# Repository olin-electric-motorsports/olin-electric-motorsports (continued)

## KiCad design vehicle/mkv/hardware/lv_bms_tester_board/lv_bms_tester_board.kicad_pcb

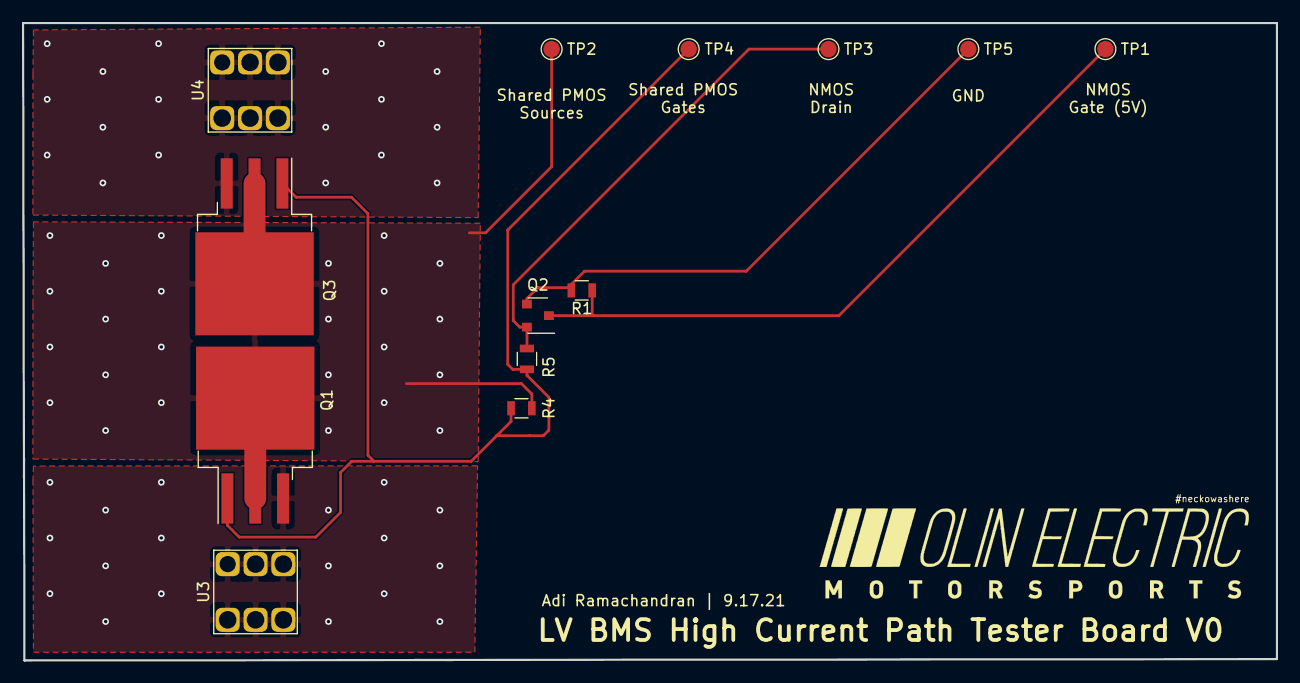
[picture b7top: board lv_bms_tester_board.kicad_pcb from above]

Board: 4 copper layers, 114.3 x 58.1 mm, 13 parts (0 on the bottom side), 7 nets.

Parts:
Q1, Q3: SQM110P06; TO-263-3-TabPin2
Q2: MMBF170; SOT-23-3_OEM
R1: R_100K; R_0805_OEM
R4: R_10K; R_0805_OEM
R5: R_10; R_0805_OEM
TP1, TP2, TP3, TP4, TP5: Test_Point_SMD; TestPoint_Pad_D1.5mm
U3, U4: redcube-7461057; redcube_pressfit_6pin

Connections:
GND: Q2.2, R1.2, TP5.1
unnamed: Q1.1, Q3.1, R4.2, R5.1, TP4.1
unnamed: Q1.2, Q3.2, R4.1, TP2.1
unnamed: Q1.3, U3.1
unnamed: Q2.1, R1.1, TP1.1
unnamed: Q2.3, R5.2, TP3.1
unnamed: Q3.3, U4.1

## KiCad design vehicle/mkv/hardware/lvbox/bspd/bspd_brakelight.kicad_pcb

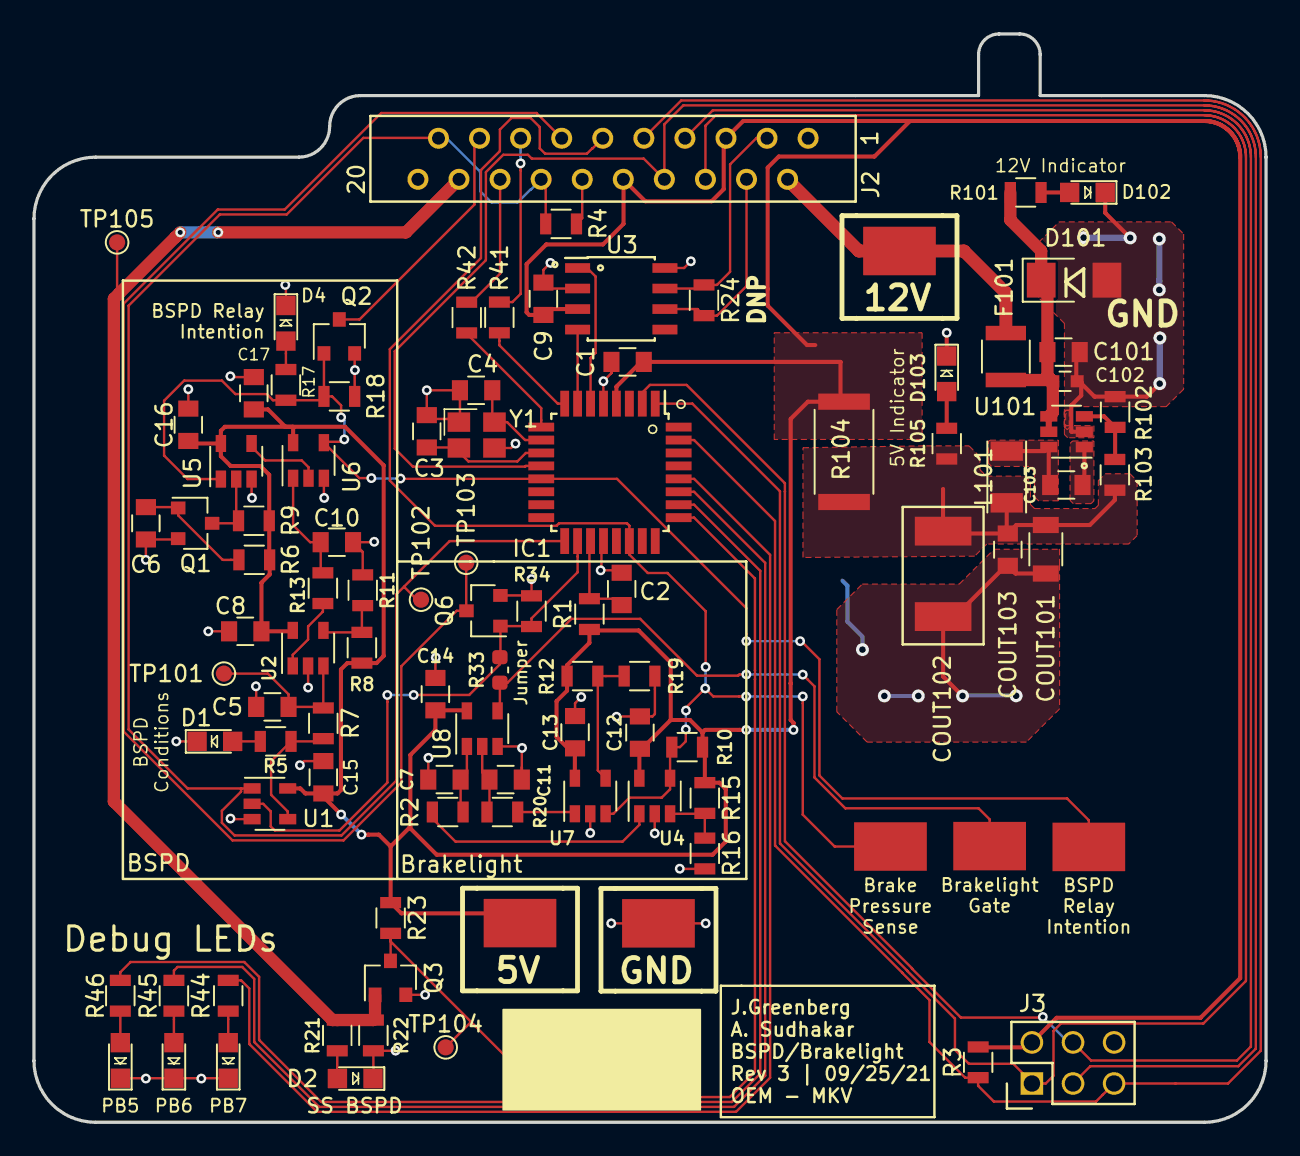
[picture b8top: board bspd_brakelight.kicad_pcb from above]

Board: 2 copper layers, 76.2 x 67.3 mm, 97 parts (0 on the bottom side), 57 nets.

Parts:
C1, C6, C8, C9, C12, C13, C14, C15, C16, C17, C101, C103: C_0.1uF; C_0805_OEM
C2: C_100pF; C_0805_OEM
C3, C4: C_30pF; C_0805_OEM
C5: C_10uF; C_0805_OEM
C7, C10, C11: C_1uF; C_0805_OEM
C102: C_2.2uF; C_0603
COUT101: C_22uF; C_1206_OEM
COUT102: C_33uF; Fuse_1812
COUT103: C_47uF; C_0805_OEM
D1, D2, D4, D5, D12, D13, D102, D103: LED_0805; LED_0805_OEM
D101: D_Zener_18V; DO-214AA
F101: F_500mA_16V; Fuse_1210
IC1: ATMEGA16M1; TQFP-32_7x7mm_Pitch0.8mm
J2: MM_F_RA_20; micromatch_female_ra_20
J3: CONN_02X03; Pin_Header_Straight_2x03
L101: L_100uH; L_100uH_OEM
Q1, Q2, Q3, Q6: SSM3K333R; SOT-23F
R1: R_100; R_0805_OEM
R2, R6, R8, R10, R11, R13, R15, R18, R20, R21, R23, R34: R_10K; R_0805_OEM
R3: R_10k; R_0805_OEM
R4, R9, R22, R103: R_100K; R_0805_OEM
R5, R17, R41, R42, R44, R45, R46, R105: R_200; R_0805_OEM
R7: R_71.5K; R_0805_OEM
R12: R_2.2K; R_0805_OEM
R16, R101: R_1K; R_0805_OEM
R19: R_499; R_0805_OEM
R24: R_120_DNP; R_0805_OEM
R33: R_0; R_0603_1608Metric
R102: R_25K; R_0805_OEM
R104: R_0_2512; R_2512_OEM
TP1, TP2, TP3, TP4, TP5, TP6: Test_Point_SMD
TP101, TP102, TP103, TP104, TP105: Test_Point_SMD; TestPoint_Pad_D1.0mm
U1: SN74LVC1G08; SOT-23-5_OEM
U2, U4, U7: MCP6001; SOT-23-5_OEM
U3: CAN_Transceiver; SOIC-8_3.9x4.9mm_Pitch1.27mm_OEM
U5, U6: SN74LVC1G02; SOT-23-5_OEM
U8: SN74LVC1G32; SOT-23-5_OEM
U101: TPS560430YF; SOT-23-6_OEM
Y1: Crystal_SMD; Crystal_SMD_FA238

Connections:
+12V: F101.2, J2.2, TP4.1
/BRAKELIGHT_GATE: IC1.18, Q6.1, R33.1, R34.1, U1.2
/BRAKELIGHT_LSD: J2.13, Q6.3, TP103.1
/BRAKE_PRESSURE_SENSE: IC1.22, J2.11, R10.2, TP1.1, U4.4, U7.3
/BSPD_CURRENT_SENSE: IC1.17, J2.14, J2.19, R4.2, TP102.1, U1.1
/BSPD_RELAY_INTENTION: IC1.13, Q2.1, R17.1, R18.1, TP3.1, U5.1, U6.4
/BSPD_RELAY_LSD: J2.17, Q2.3
/CAN_HIGH: J2.3, R24.1, U3.7
/CAN_LOW: J2.4, R24.2, U3.6
/DEBUG_LED_1: IC1.26, R46.1
/DEBUG_LED_2: IC1.27, R45.1
/DEBUG_LED_3: IC1.28, R44.1
/MISO: IC1.1, J2.6, J3.1
/MOSI: IC1.2, J2.7, J3.4
/RESET: IC1.31, J2.9, J3.5, R3.2
/RJ45_LED_G: J2.15, R41.1
/RJ45_LED_O: J2.16, R42.2
/RXCAN: IC1.7, U3.4
/SCK: IC1.12, J2.8, J3.3
/SHUTDOWN_SENSE_BSPD: J2.18, Q3.1, R21.1, R22.2, TP105.1
/TXCAN: IC1.6, U3.1
/~SHUTDOWN_SENSE_BSPD_PIN: IC1.25, Q3.3, R23.2, TP104.1
GND: C1.2, C2.2, C3.2, C4.2, C5.2, C6.2, C7.2, C8.2, C9.2, C10.2, C11.2, C12.2, C13.2, C14.2, C15.2, C16.2, C17.2, C101.2, C102.2, COUT101.2, COUT102.2, COUT103.2, D1.1, D2.1, D4.1, D5.1, D12.1, D13.1, D101.2, D102.1, D103.1, IC1.5, IC1.20, J2.1, J2.12, J2.20, J3.6, Q1.2, Q2.2, Q3.2, Q6.2, R4.1, R11.2, R16.2, R18.2, R19.1, R22.1, R34.2, R102.2, TP6.1, U1.3, U2.2, U3.2, U3.8, U4.2, U5.3, U6.3, U7.2, U8.3, U101.2, Y1.2, Y1.4
unnamed: C2.1, IC1.19, R1.2
unnamed: C3.1, IC1.11, Y1.1
unnamed: C4.1, IC1.10, Y1.3
unnamed: C5.1, R7.2, TP101.1, U2.3
unnamed: C6.1, Q1.1, R6.2
unnamed: C7.1, R2.1, U8.1
unnamed: C10.1, R13.1, U6.1
unnamed: C11.1, R20.1, U8.2
unnamed: C101.1, C102.1, D101.1, F101.1, R101.1, U101.4, U101.5
unnamed: C103.1, L101.1, U101.6
unnamed: C103.2, U101.1
unnamed: COUT101.1, COUT102.1, COUT103.1, L101.2, R103.1, R104.2, R105.1
unnamed: D1.2, R5.2
unnamed: D2.2, R21.2
unnamed: D4.2, R17.2
unnamed: D5.2, R44.2
unnamed: D12.2, R45.2
unnamed: D13.2, R46.2
unnamed: D102.2, R101.2
unnamed: D103.2, R105.2
unnamed: IC1.8, R41.2
unnamed: IC1.9, R42.1
unnamed: Q1.3, R9.1, U5.2
unnamed: R2.2, U4.1
unnamed: R5.1, R7.1, U1.4
unnamed: R8.2, R11.1, U2.4
unnamed: R12.1, R19.2, U7.4
unnamed: R13.2, U2.1
unnamed: R15.2, R16.1, U4.3
unnamed: R20.2, U7.1
unnamed: R33.2, TP2.1, U8.4
unnamed: R102.1, R103.2, U101.3
unnamed: U5.4, U6.2
VCC: C1.1, C8.1, C9.1, C12.1, C13.1, C14.1, C15.1, C16.1, C17.1, IC1.4, J2.5, J2.10, J3.2, R1.1, R3.1, R6.1, R8.1, R9.2, R10.1, R12.2, R15.1, R23.1, R104.1, TP5.1, U1.5, U2.5, U3.3, U4.5, U5.5, U6.5, U7.5, U8.5

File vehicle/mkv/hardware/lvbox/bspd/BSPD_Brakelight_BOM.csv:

Reference, Quantity, Value, Footprint, Datasheet, MFN, MPN, Package, PurchasingLink, Digi-key Part Number, Link, Purchasing Link
C10 C7 C11 ,3,"C_1uF","footprints:C_0805_OEM","http://www.samsungsem.com/kr/support/product-search/mlcc/__i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","DK","1276-2887-1-ND","","https://www.digikey.com/product-detail/en/samsung-electro-me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","","",""
C102 ,1,"C_2.2uF","footprints:C_0603_1608Metric","http://www.yageo.com/documents/recent/UPY-GPHC_X5R_4V-to-50V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","DK","311-1451-1-ND","","https://www.digikey.com/product-detail/en/yageo/CC0603KRX5R6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","","",""
C2 ,1,"C_100pF","footprints:C_0805_OEM","https://katalog.we-online.de/pbs/datasheet/885012007057.pdf","DK","732-7852-1-ND","Value","https://www.digikey.com/product-detail/en/wurth-electronics-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","","",""
C4 C3 ,2,"C_30pF","footprints:C_0805_OEM","https://media.digikey.com/pdf/Data%20Sheets/Samsung%20PDFs/C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","DK","1276-1130-1-ND","Value","https://www.digikey.com/product-detail/en/samsung-electro-me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","","",""
C5 ,1,"C_10uF","footprints:C_0805_OEM","http://www.samsungsem.com/kr/support/product-search/mlcc/__i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","DK","1276-1052-1-ND","","https://www.digikey.com/product-detail/en/samsung-electro-me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","","",""
C9 C8 C6 C1 C101 C103 C13 C12 C14 C15 C17 C16 ,12,"C_0.1uF","footprints:C_0805_OEM","http://datasheets.avx.com/X7RDielectric.pdf","DK","478-3352-1-ND","Value","https://www.digikey.com/products/en?keywords=478-3352-1-ND","","",""
COUT101 ,1,"C_22uF","footprints:C_1206_OEM","https://product.tdk.com/info/en/catalog/datasheets/mlcc_comm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","DK","445-11693-1-ND","","https://www.digikey.com/product-detail/en/tdk-corporation/C3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","","",""
COUT102 ,1,"C_33uF","footprints:Fuse_1812","","DK","445-3924-1-ND","","https://www.digikey.com/product-detail/en/tdk-corporation/C4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","","",""
COUT103 ,1,"C_47uF","footprints:C_0805_OEM","http://www.samsungsem.com/kr/support/product-search/mlcc/__i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","DK","1276-6467-1-ND","","https://www.digikey.com/product-detail/en/samsung-electro-me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","","",""
D1 D4 D5 D12 D13 D103 D102 D2 ,8,"LED_0805","footprints:LED_0805_OEM","http://www.osram-os.com/Graphics/XPic9/00078860_0.pdf","DK","475-1410-1-ND","","https://www.digikey.com/products/en?keywords=475-1410-1-ND","","",""
D101 ,1,"D_Zener_18V","footprints:DO-214AA","http://www.mccsemi.com/up_pdf/SMBJ5338B-SMBJ5388B(SMB).pdf","DK","SMBJ5355B-TPMSCT-ND","","https://www.digikey.com/products/en?keywords=SMBJ5355B-TPMSCT-ND","","",""
F101 ,1,"F_500mA_16V","footprints:Fuse_1210","https://belfuse.com/resources/CircuitProtection/datasheets/0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","DK","507-1786-1-ND","","https://www.digikey.com/product-detail/en/bel-fuse-inc/0ZCH0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","","",""
IC1 ,1,"ATMEGA16M1","footprints:TQFP-32_7x7mm_Pitch0.8mm","http://ww1.microchip.com/downloads/en/DeviceDoc/Atmel-8209-8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","DK","ATMEGA16M1-AU-ND","Value","https://www.digikey.com/product-detail/en/atmel/ATMEGA16M1-A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","","",""
J2 ,1,"MM_F_RA_20","footprints:micromatch_female_ra_20","http://www.te.com/commerce/DocumentDelivery/DDEController?Ac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","TE","2-338070-0","","http://www.te.com/usa-en/product-2-338070-0.html","","",""
J3 ,1,"CONN_02X03","footprints:Pin_Header_Straight_2x03","http://portal.fciconnect.com/Comergent//fci/drawing/67996.pdf","DK","609-3234-ND","Value","https://www.digikey.com/product-detail/en/amphenol-fci/67997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","","",""
L101 ,1,"L_100uH","footprints:L_100uH_OEM","","DK","445-15759-1-ND","","https://www.digikey.com/product-detail/en/tdk-corporation/NL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","","https://www.digikey.com/product-detail/en/tdk-corporation/NL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",""
Q1 Q2 Q6 Q3 ,4,"SSM3K333R","footprints:SOT-23F","https://drive.google.com/drive/folders/0B-V-iZf33Y4GNzhDQTJZanJRbVk","DK","SSM3K333RLFCT-ND","","https://www.digikey.com/product-detail/en/toshiba-semiconduc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","","",""
R1 ,1,"R_100","footprints:R_0805_OEM","https://www.seielect.com/Catalog/SEI-rncp.pdf","DK","RNCP0805FTD100RCT-ND","Value","https://www.digikey.com/products/en?keywords=RNCP0805FTD100RCT-ND","","",""
R102 ,1,"R_25K","footprints:R_0805_OEM","","DK","A124124CT-ND","","https://www.digikey.com/product-detail/en/te-connectivity-pa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","CPF-A-0805B25KE","",""
R104 ,1,"R_0_2512","footprints:R_2512_OEM","http://www.te.com/commerce/DocumentDelivery/DDEController?Ac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","DK","A121322CT-ND","","https://www.digikey.com/products/en?keywords=A121322CT-ND","","",""
R12 ,1,"R_2.2K","footprints:R_0805_OEM","https://www.seielect.com/Catalog/SEI-RMCF_RMCP.pdf","DK","RMCF0805FT2K20CT-ND","","https://www.digikey.com/product-detail/en/stackpole-electron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","","",""
R16 R101 ,2,"R_1K","footprints:R_0805_OEM","https://www.seielect.com/Catalog/SEI-rncp.pdf","DK","RNCP0805FTD1K00CT-ND","","https://www.digikey.com/products/en?keywords=RNCP0805FTD1K00CT-ND","","",""
R19 ,1,"R_499","footprints:R_0805_OEM","https://industrial.panasonic.com/cdbs/www-data/pdf/RDA0000/A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","DK","P499CCT-ND","","https://www.digikey.com/product-detail/en/panasonic-electron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","","",""
R24 ,1,"R_120_DNP","footprints:R_0805_OEM","","DK","667-ERJ-6ENF1200V","","https://www.mouser.com/ProductDetail/Panasonic-Industrial-De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","","",""
R3 ,1,"R_10k","footprints:R_0805_OEM","http://www.bourns.com/data/global/pdfs/CRS.pdf","DK","CRS0805-FX-1002ELFCT-ND","Value","https://www.digikey.com/products/en?keywords=CRS0805-FX-1002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","","",""
R33 ,1,"R_0","footprints:R_0603_1608Metric","http://industrial.panasonic.com/www-cgi/jvcr13pz.cgi?E+PZ+3+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","DK","P0.0GCT-ND","","https://www.digikey.com/product-detail/en/panasonic-electron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","","",""
R4 R9 R103 R22 ,4,"R_100K","footprints:R_0805_OEM","https://industrial.panasonic.com/cdbs/www-data/pdf/RDA0000/A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","DK","P100KCCT-ND","","https://www.digikey.com/product-detail/en/panasonic-electron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","","",""
R5 R17 R41 R42 R44 R45 R46 R105 ,8,"R_200","footprints:R_0805_OEM","https://www.seielect.com/Catalog/SEI-RMCF_RMCP.pdf","DK","RMCF0805JT200RCT-ND","","https://www.digikey.com/products/en?keywords=RMCF0805JT200RCT-ND","","",""
R7 ,1,"R_71.5K","footprints:R_0805_OEM","https://industrial.panasonic.com/cdbs/www-data/pdf/RDM0000/A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","DK","P1.07KDACT-ND","","https://www.digikey.com/product-detail/en/panasonic-electron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","","",""
R8 R11 R13 R6 R18 R34 R15 R10 R2 R20 R23 R21 ,12,"R_10K","footprints:R_0805_OEM","http://www.bourns.com/data/global/pdfs/CRS.pdf","DK","CRS0805-FX-1002ELFCT-ND","","https://www.digikey.com/products/en?keywords=CRS0805-FX-1002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","","",""
TP1 TP2 TP3 TP4 TP5 TP6 ,6,"Test_Point_SMD","footprints:Test_Point_SMD",""
U1 ,1,"SN74LVC1G08","footprints:SOT-23-5_OEM","http://www.ti.com/lit/ds/symlink/sn74lvc1g08.pdf","DK","296-11601-2-ND","","https://www.digikey.com/product-detail/en/texas-instruments/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","","",""
U101 ,1,"TPS560430YF","footprints:SOT-23-6_OEM","","DK","TPS560430YFDBVR-ND","","https://www.digikey.com/product-detail/en/texas-instruments/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","","","https://www.digikey.com/product-detail/en/texas-instruments/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"
U2 U7 U4 ,3,"MCP6001","Package_TO_SOT_SMD:SOT-23-5","http://ww1.microchip.com/downloads/en/DeviceDoc/21733j.pdf","DK","MCP6001T-I/OTCT-ND","","https://www.digikey.com/product-detail/en/microchip-technolo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","","",""
U3 ,1,"CAN_Transceiver","footprints:SOIC-8_3.9x4.9mm_Pitch1.27mm_OEM","http://www.microchip.com/mymicrochip/filehandler.aspx?ddocna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","DK","MCP2561-E/SN-ND","Value","https://www.digikey.com/products/en?keywords=mcp2561-e%2Fsn","","",""
U5 U6 ,2,"SN74LVC1G02","footprints:SOT-23-5_OEM","http://www.ti.com/lit/ds/symlink/sn74lvc1g02.pdf","DK","296-11597-1-ND","","https://www.digikey.com/product-detail/en/texas-instruments/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","","",""
U8 ,1,"SN74LVC1G32","footprints:SOT-23-5_OEM","http://www.ti.com/lit/ds/symlink/sn74lvc1g32.pdf","DK","296-9847-1-ND","","https://www.digikey.com/product-detail/en/texas-instruments/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","","",""
Y1 ,1,"Crystal_SMD","footprints:Crystal_SMD_FA238","http://www.txccorp.com/download/products/quartz_crystals/201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","DK","887-1125-1-ND","Value","https://www.digikey.com/product-detail/en/txc-corporation/7M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","","",""
